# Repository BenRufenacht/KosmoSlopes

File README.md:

# KosmoSlopes
 Kosmo Version of the Kassutronics Slope Module

[Build Docs from Kassutronics](https://github.com/kassu/kassutronics/blob/master/documentation/Slope/Kassutronics_Slope_Build_Docs_2.0B.pdf)

Status:   
February 2023 - First run of manufacturing found some minor mistakes that were fixed, but the updates to the main board have not been tested.

License:  
[CC-BY-SA](https://creativecommons.org/licenses/by-sa/3.0/)

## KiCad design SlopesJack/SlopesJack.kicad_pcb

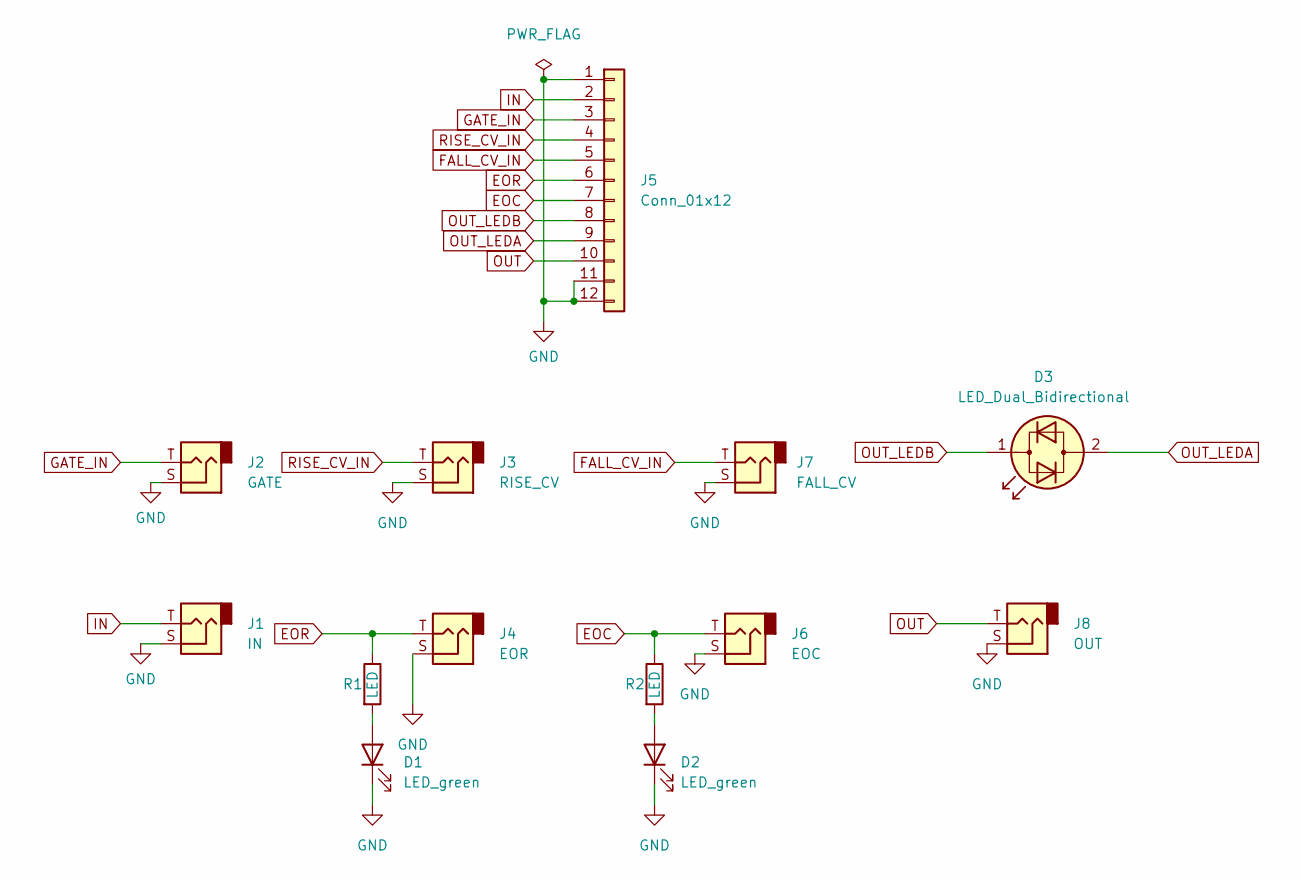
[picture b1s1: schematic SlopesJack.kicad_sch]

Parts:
D1, D2: LED_green; LED_D5.0mm
D3: LED_Dual_Bidirectional; LED_D5.0mm
J1: IN; Jack_6.35mm_PJ_629HAN_slots
J2: GATE; Jack_6.35mm_PJ_629HAN_slots
J3: RISE_CV; Jack_6.35mm_PJ_629HAN_slots
J4: EOR; Jack_6.35mm_PJ_629HAN_slots
J5: Conn_01x12; PinHeader_1x12_P2.54mm_Vertical
J6: EOC; Jack_6.35mm_PJ_629HAN_slots
J7: FALL_CV; Jack_6.35mm_PJ_629HAN_slots
J8: OUT; Jack_6.35mm_PJ_629HAN_slots
R1, R2: LED; R_Axial_DIN0207_L6.3mm_D2.5mm_P10.16mm_Horizontal

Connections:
EOC: J5.7, J6.T, R2.1
EOR: J4.T, J5.6, R1.1
FALL_CV_IN: J5.5, J7.T
GATE_IN: J2.T, J5.3
GND: D1.1 (K), D2.1 (K), J1.S, J2.S, J3.S, J4.S, J5.1, J5.11, J5.12, J6.S, J7.S, J8.S
IN: J1.T, J5.2
unnamed: D1.2 (A), R1.2
unnamed: D2.2 (A), R2.2
OUT: J5.10, J8.T
OUT_LEDA: D3.2 (AK), J5.9
OUT_LEDB: D3.1 (KA), J5.8
RISE_CV_IN: J3.T, J5.4

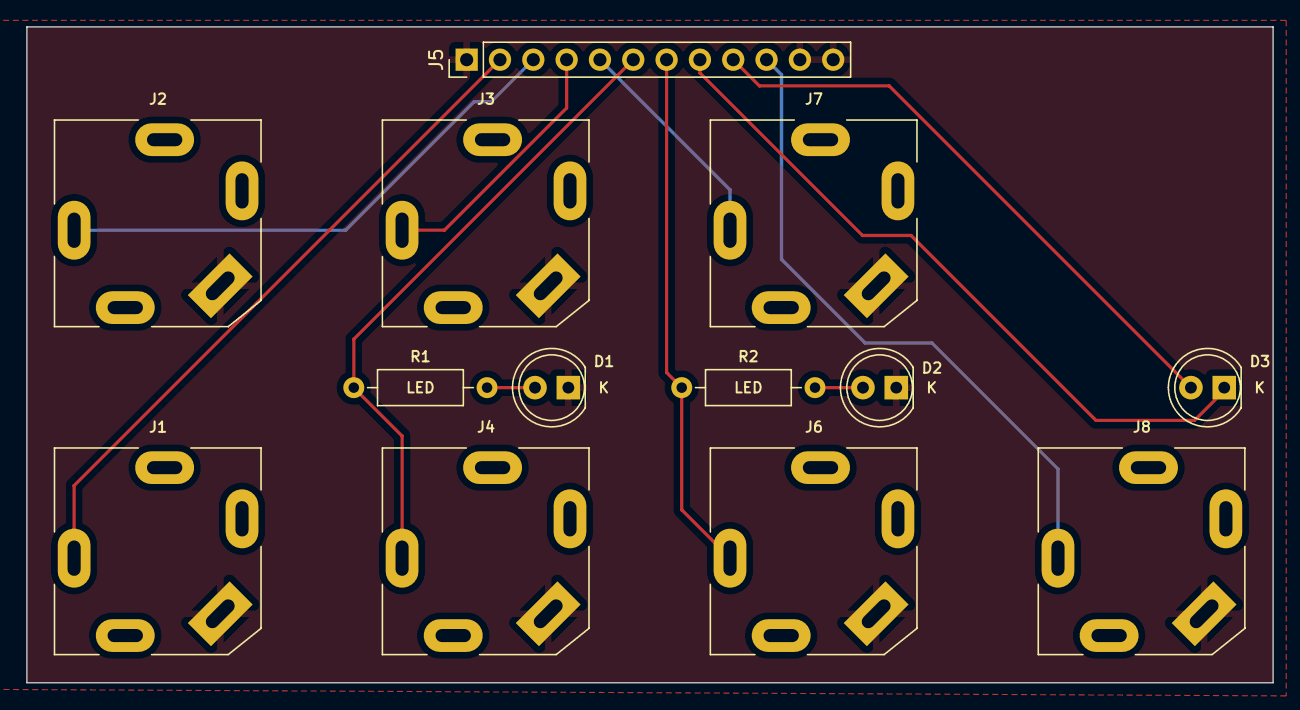
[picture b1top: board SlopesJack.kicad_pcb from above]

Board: 2 copper layers, 95.0 x 50.0 mm, 13 parts (0 on the bottom side), 12 nets.

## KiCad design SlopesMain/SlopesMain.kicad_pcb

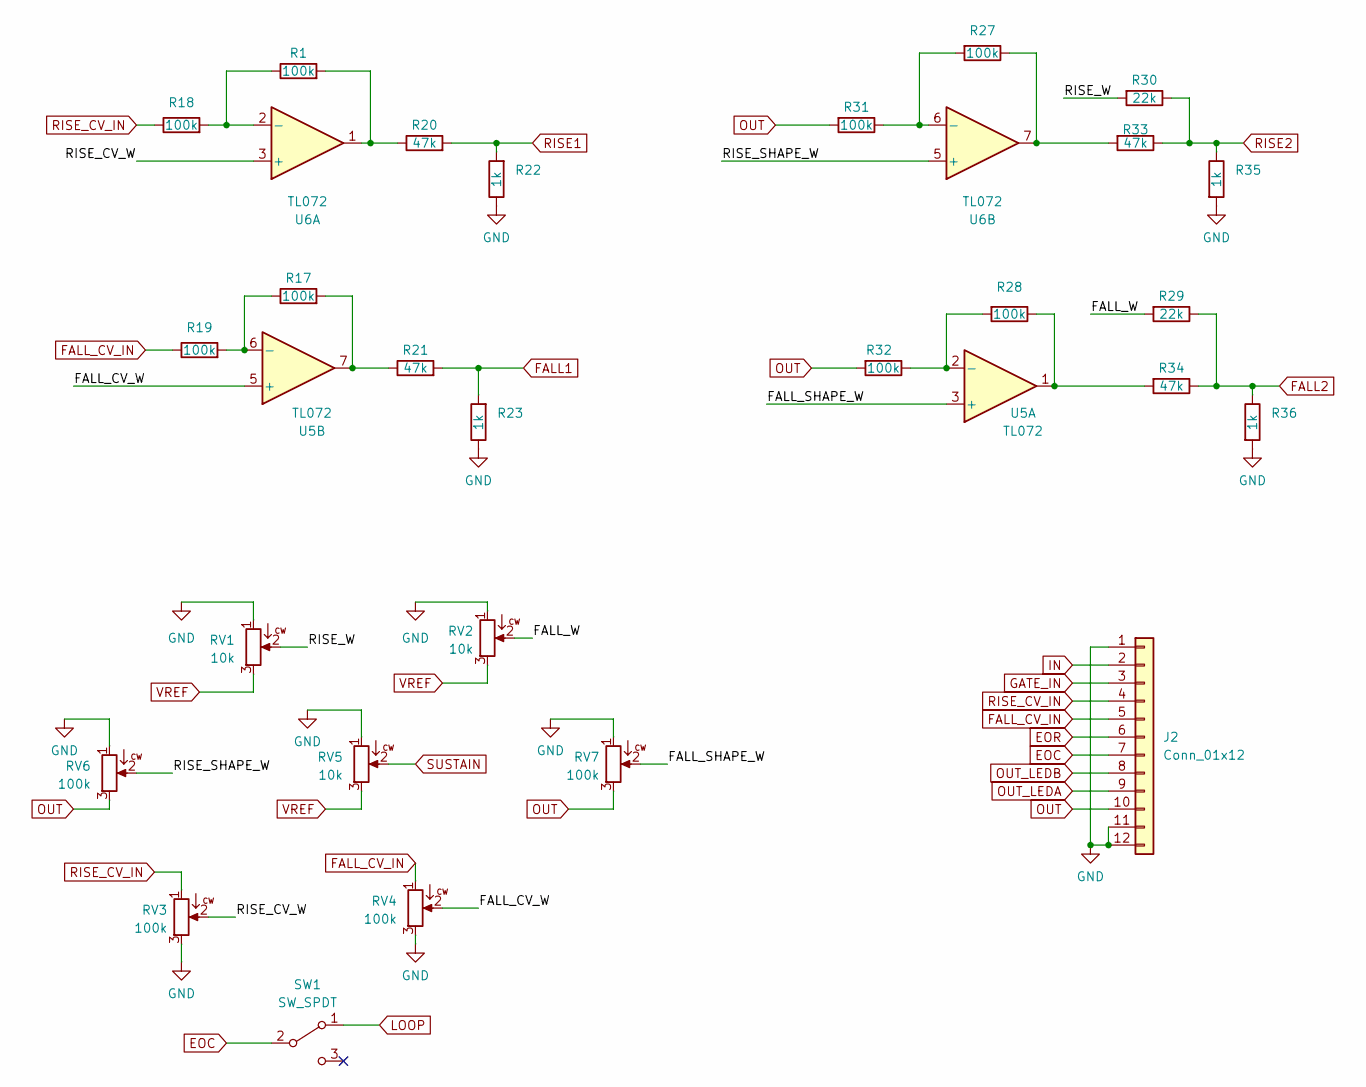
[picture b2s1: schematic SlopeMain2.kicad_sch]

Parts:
J2: Conn_01x12; PinSocket_1x12_P2.54mm_Vertical
R1, R17, R18, R19, R27, R28, R31, R32: 100k; R_Axial_DIN0207_L6.3mm_D2.5mm_P10.16mm_Horizontal
R20, R21, R33, R34: 47k; R_Axial_DIN0207_L6.3mm_D2.5mm_P10.16mm_Horizontal
R22, R23, R35, R36: 1k; R_Axial_DIN0207_L6.3mm_D2.5mm_P10.16mm_Horizontal
R29, R30: 22k; R_Axial_DIN0207_L6.3mm_D2.5mm_P10.16mm_Horizontal
RV1, RV2, RV5: 10k; Potentiometer_Alpha_RD901F-40-00D_Single_Vertical_centered
RV3, RV4, RV6, RV7: 100k; Potentiometer_Alpha_RD901F-40-00D_Single_Vertical_centered
SW1: SW_SPDT; SPDT-toggle-switch-1M-series
U5, U6: TL072; DIP-8_W7.62mm_Socket_LongPads

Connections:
/Slope Main 2/FALL_CV_W: RV4.2, U5.5 (+)
/Slope Main 2/FALL_SHAPE_W: RV7.2, U5.3 (+)
/Slope Main 2/FALL_W: R29.2, RV2.2
/Slope Main 2/RISE_CV_W: RV3.2, U6.3 (+)
/Slope Main 2/RISE_SHAPE_W: RV6.2, U6.5 (+)
/Slope Main 2/RISE_W: R30.2, RV1.2
EOC: J2.7, SW1.2 (B); also elsewhere on the board
EOR: J2.6; also elsewhere on the board
FALL1: R21.2, R23.2; also elsewhere on the board
FALL2: R29.1, R34.1, R36.1; also elsewhere on the board
FALL_CV_IN: J2.5, R19.1, RV4.1
GATE_IN: J2.3; also elsewhere on the board
GND: J2.1, J2.11, J2.12, R22.1, R23.1, R35.2, R36.2, RV1.1, RV2.1, RV3.3, RV4.3, RV5.1, RV6.1, RV7.1; also elsewhere on the board
IN: J2.2; also elsewhere on the board
LOOP: SW1.1 (A); also elsewhere on the board
unnamed: R1.2, R20.1, U6.1
unnamed: R17.2, R21.1, U5.7
unnamed: R27.1, R33.2, U6.7
unnamed: R28.1, R34.2, U5.1
unnamed: R28.2, R32.1, U5.2 (-)
unnamed: R17.1, R19.2, U5.6 (-)
unnamed: R1.1, R18.2, U6.2 (-)
unnamed: R27.2, R31.1, U6.6 (-)
OUT: J2.10, R31.2, R32.2, RV6.3, RV7.3; also elsewhere on the board
OUT_LEDA: J2.9; also elsewhere on the board
OUT_LEDB: J2.8; also elsewhere on the board
RISE1: R20.2, R22.2; also elsewhere on the board
RISE2: R30.1, R33.1, R35.1; also elsewhere on the board
RISE_CV_IN: J2.4, R18.1, RV3.1
SUSTAIN: RV5.2; also elsewhere on the board
VREF: RV1.3, RV2.3, RV5.3; also elsewhere on the board

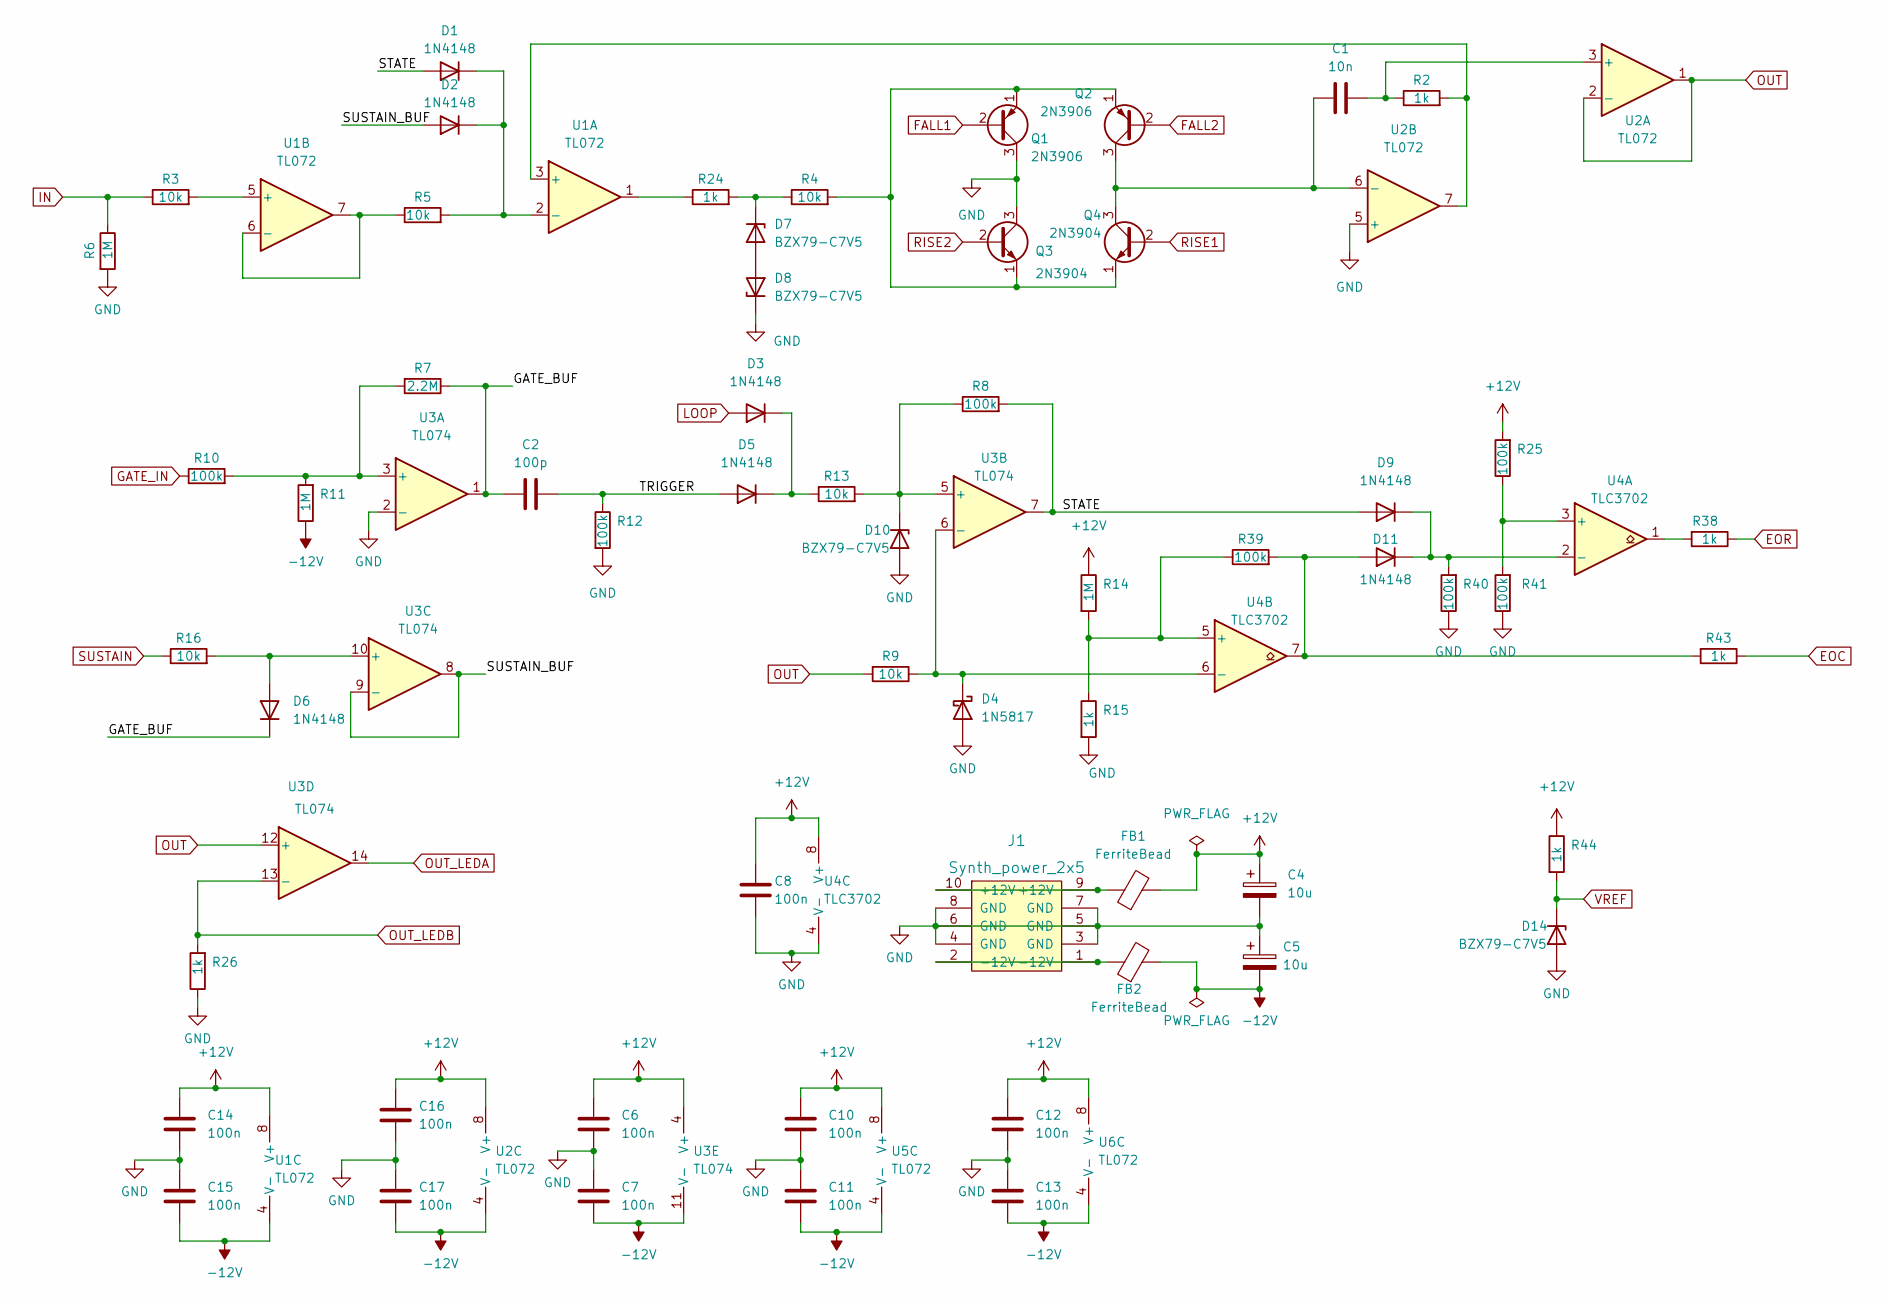
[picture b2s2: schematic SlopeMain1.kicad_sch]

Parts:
C1: 10n; C_Rect_L7.2mm_W2.5mm_P5.00mm_FKS2_FKP2_MKS2_MKP2
C2: 100p; C_Rect_L7.2mm_W2.5mm_P5.00mm_FKS2_FKP2_MKS2_MKP2
C4, C5: 10u; CP_Radial_D6.3mm_P2.50mm
C6, C7, C8, C10, C11, C12, C13, C14, C15, C16, C17: 100n; C_Rect_L7.2mm_W2.5mm_P5.00mm_FKS2_FKP2_MKS2_MKP2
D1, D2, D3, D5, D6, D9, D11: 1N4148; D_DO-35_SOD27_P7.62mm_Horizontal
D4: 1N5817; D_DO-41_SOD81_P10.16mm_Horizontal
D7, D8, D10, D14: BZX79-C7V5; D_DO-41_SOD81_P10.16mm_Horizontal
FB1, FB2: FerriteBead; L_Axial_L5.0mm_D3.6mm_P10.00mm_Horizontal_Murata_BL01RN1A2A2
J1: Synth_power_2x5; Power_Header
Q1, Q2: 2N3906; TO-92_Inline_Wide
Q3, Q4: 2N3904; TO-92_Inline_Wide
R2, R15, R24, R26, R38, R43, R44: 1k; R_Axial_DIN0207_L6.3mm_D2.5mm_P10.16mm_Horizontal
R3, R4, R5, R9, R13, R16: 10k; R_Axial_DIN0207_L6.3mm_D2.5mm_P10.16mm_Horizontal
R6, R11, R14: 1M; R_Axial_DIN0207_L6.3mm_D2.5mm_P10.16mm_Horizontal
R7: 2.2M; R_Axial_DIN0207_L6.3mm_D2.5mm_P10.16mm_Horizontal
R8, R10, R12, R25, R39, R40, R41: 100k; R_Axial_DIN0207_L6.3mm_D2.5mm_P10.16mm_Horizontal
U1, U2, U5, U6: TL072; DIP-8_W7.62mm_Socket_LongPads
U3: TL074; DIP-14_W7.62mm_Socket_LongPads
U4: TLC3702; DIP-8_W7.62mm_Socket_LongPads

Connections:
+12V: C4.1, C6.1, C8.1, C10.1, C12.1, C14.1, C16.1, FB1.2, R14.1, R25.2, R44.1, U1.8 (V+), U2.8 (V+), U3.4 (V+), U4.8 (V+), U5.8 (V+), U6.8 (V+)
-12V: C5.2, C7.2, C11.2, C13.2, C15.2, C17.2, FB2.2, R11.1, U1.4 (V-), U2.4 (V-), U3.11 (V-), U5.4 (V-), U6.4 (V-)
/Slope Main 1/GATE_BUF: C2.1, D6.1 (K), R7.1, U3.1
/Slope Main 1/STATE: D1.2 (A), D9.2 (A), R8.2, U3.7
/Slope Main 1/SUSTAIN_BUF: D2.2 (A), U3.8, U3.9 (-)
/Slope Main 1/TRIGGER: C2.2, D5.2 (A), R12.1
EOC: R43.1; also elsewhere on the board
EOR: R38.1; also elsewhere on the board
FALL1: Q1.2 (B); also elsewhere on the board
FALL2: Q2.2 (B); also elsewhere on the board
GATE_IN: R10.1; also elsewhere on the board
GND: C4.2, C5.1, C6.2, C7.1, C8.2, C10.2, C11.1, C12.2, C13.1, C14.2, C15.1, C16.2, C17.1, D4.2 (A), D8.1 (K), D10.2 (A), D14.2 (A), J1.3 (GND), J1.4 (GND), J1.5 (GND), J1.6 (GND), J1.7 (GND), J1.8 (GND), Q1.3 (C), Q3.3 (C), R6.2, R12.2, R15.2, R26.1, R40.1, R41.1, U2.5 (+), U3.2 (-), U4.4 (V-); also elsewhere on the board
IN: R3.1, R6.1; also elsewhere on the board
LOOP: D3.2 (A); also elsewhere on the board
unnamed: D1.1 (K), D2.1 (K), R5.2, U1.2 (-)
unnamed: D3.1 (K), D5.1 (K), R13.1
unnamed: D4.1 (K), R9.1, U3.6 (-), U4.6 (_)
unnamed: D6.2 (A), R16.2, U3.10 (+)
unnamed: D7.2 (A), D8.2 (A)
unnamed: D7.1 (K), R4.1, R24.2
unnamed: D10.1 (K), R8.1, R13.2, U3.5 (+)
unnamed: D11.2 (A), R39.2, R43.2, U4.7
unnamed: D9.1 (K), D11.1 (K), R40.2, U4.2 (-)
unnamed: FB1.1, J1.9 (+12V), J1.10 (+12V)
unnamed: FB2.1, J1.1 (-12V), J1.2 (-12V)
unnamed: Q1.1 (E), Q2.1 (E), Q3.1 (E), Q4.1 (E), R4.2
unnamed: C1.1, Q2.3 (C), Q4.3 (C), U2.6 (-)
unnamed: R24.1, U1.1
unnamed: R38.2, U4.1
unnamed: R2.2, U1.3 (+), U2.7
unnamed: R3.2, U1.5 (+)
unnamed: R5.1, U1.6 (-), U1.7
unnamed: C1.2, R2.1, U2.3 (+)
unnamed: R7.2, R10.2, R11.2, U3.3 (+)
unnamed: R25.1, R41.2, U4.3 (+)
unnamed: R14.2, R15.1, R39.1, U4.5 (+)
OUT: R9.2, U2.1, U2.2 (-), U3.12 (+); also elsewhere on the board
OUT_LEDA: U3.14; also elsewhere on the board
OUT_LEDB: R26.2, U3.13 (-); also elsewhere on the board
RISE1: Q4.2 (B); also elsewhere on the board
RISE2: Q3.2 (B); also elsewhere on the board
SUSTAIN: R16.1; also elsewhere on the board
VREF: D14.1 (K), R44.2; also elsewhere on the board

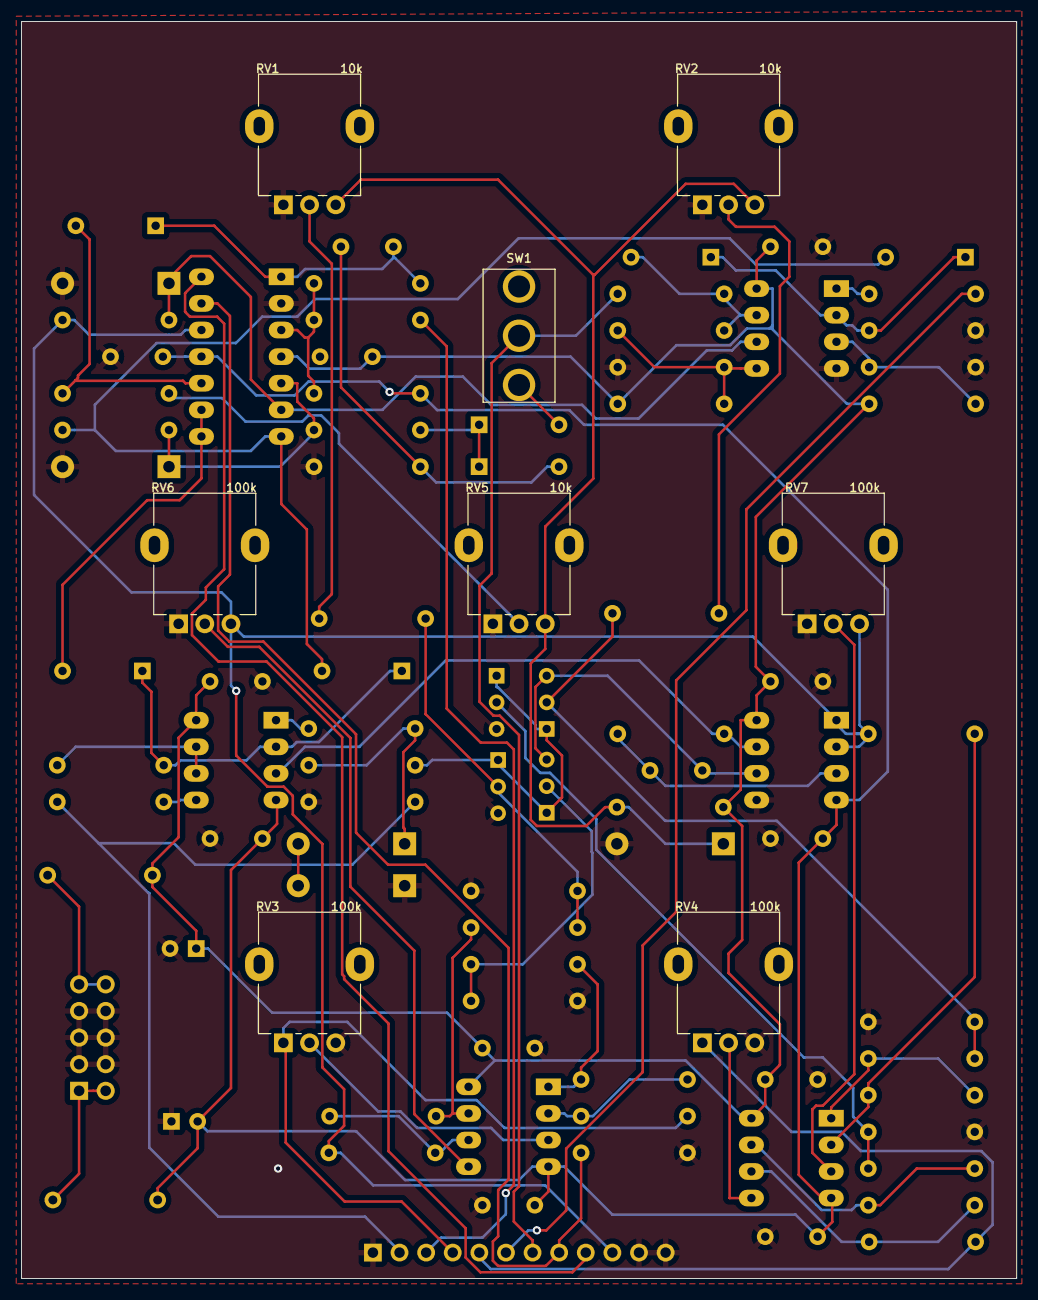
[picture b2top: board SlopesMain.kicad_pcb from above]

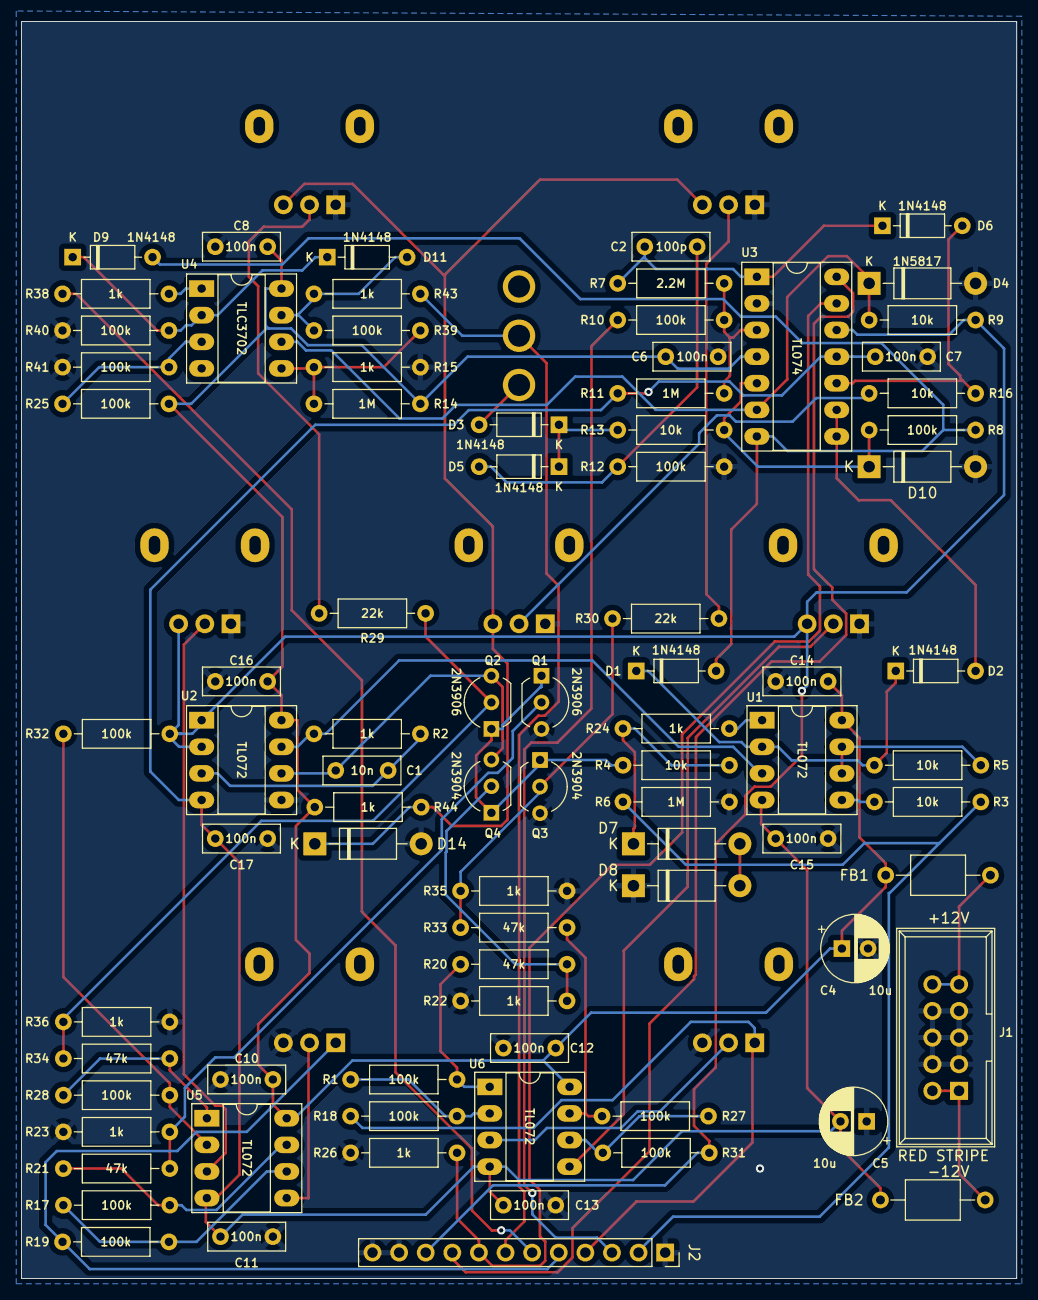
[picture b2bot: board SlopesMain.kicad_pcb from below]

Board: 2 copper layers, 95.0 x 120.0 mm, 91 parts (83 on the bottom side), 59 nets.

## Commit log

2023-03-18 Updated Schematic
